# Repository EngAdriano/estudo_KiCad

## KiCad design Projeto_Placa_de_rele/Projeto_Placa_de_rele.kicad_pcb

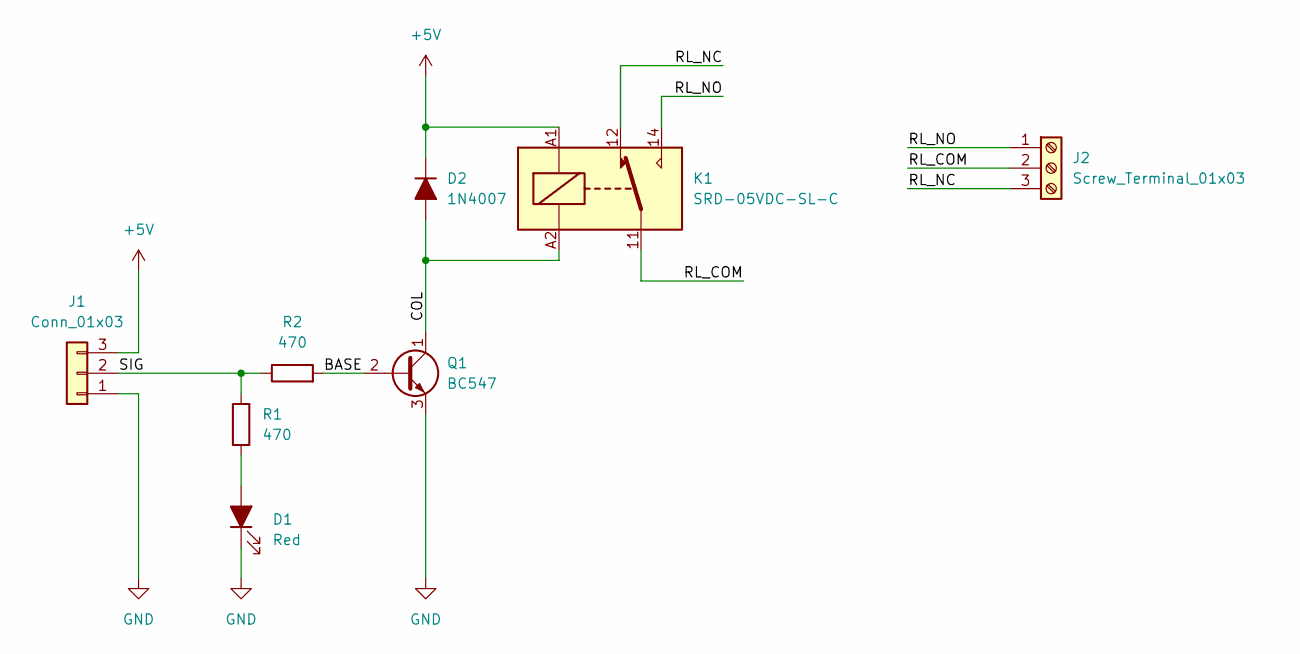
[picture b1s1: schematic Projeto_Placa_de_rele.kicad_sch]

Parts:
D1: Red; LED_D5.0mm
D2: 1N4007; D_DO-41_SOD81_P10.16mm_Horizontal
J1: Conn_01x03; PinHeader_1x03_P2.54mm_Vertical
J2: Screw_Terminal_01x03; TerminalBlock_Phoenix_MKDS-1,5-3-5.08_1x03_P5.08mm_Horizont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
K1: SRD-05VDC-SL-C; Relay_SPDT_Finder_36.11
Q1: BC547; TO-92L_Inline_Wide
R1, R2: 470; R_Axial_DIN0207_L6.3mm_D2.5mm_P10.16mm_Horizontal

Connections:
+5V: D2.1 (K), J1.3, K1.A1
/BASE: Q1.2 (B), R2.2
/COL: D2.2 (A), K1.A2, Q1.1 (C)
/RL_COM: J2.2, K1.11
/RL_NC: J2.3, K1.12
/RL_NO: J2.1, K1.14
/SIG: J1.2, R1.2, R2.1
GND: D1.1 (K), J1.1, Q1.3 (E)
unnamed: D1.2 (A), R1.1

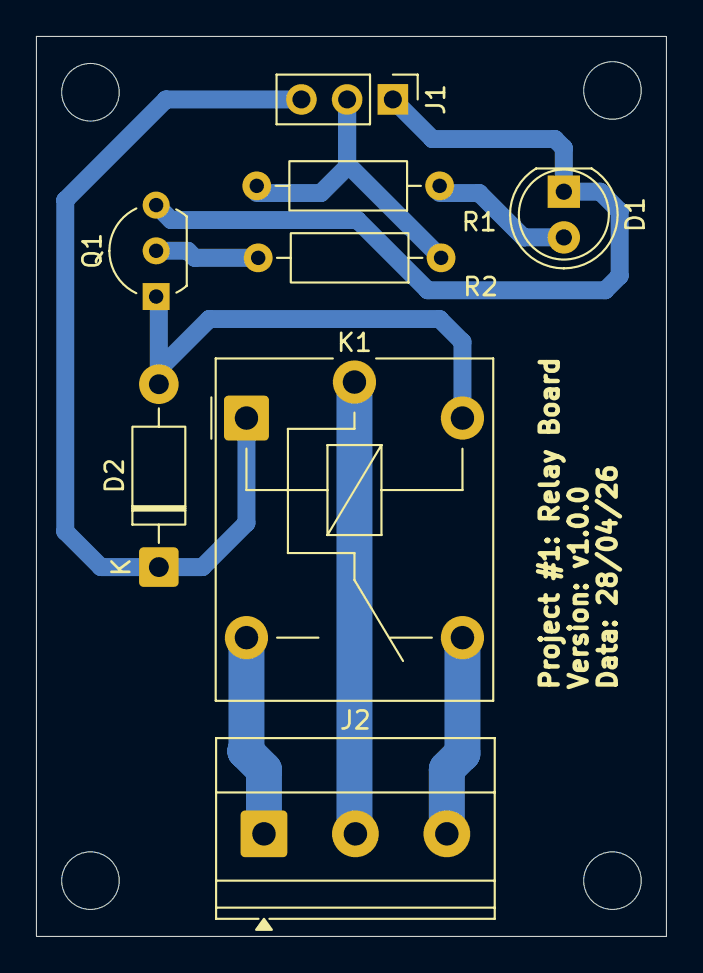
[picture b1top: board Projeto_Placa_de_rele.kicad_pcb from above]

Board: 2 copper layers, 35.0 x 50.0 mm, 8 parts (0 on the bottom side), 9 nets.

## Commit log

2026-03-09 Projeto de estudo: Placa de relé
2026-03-11 Atualização
2026-03-24 Atualização kicad10
2026-04-28 Atualização Placa Relé.
2026-04-28 Novo projeto microcontrolador face dupla
2026-05-01 Esquemático fonte + MCU
